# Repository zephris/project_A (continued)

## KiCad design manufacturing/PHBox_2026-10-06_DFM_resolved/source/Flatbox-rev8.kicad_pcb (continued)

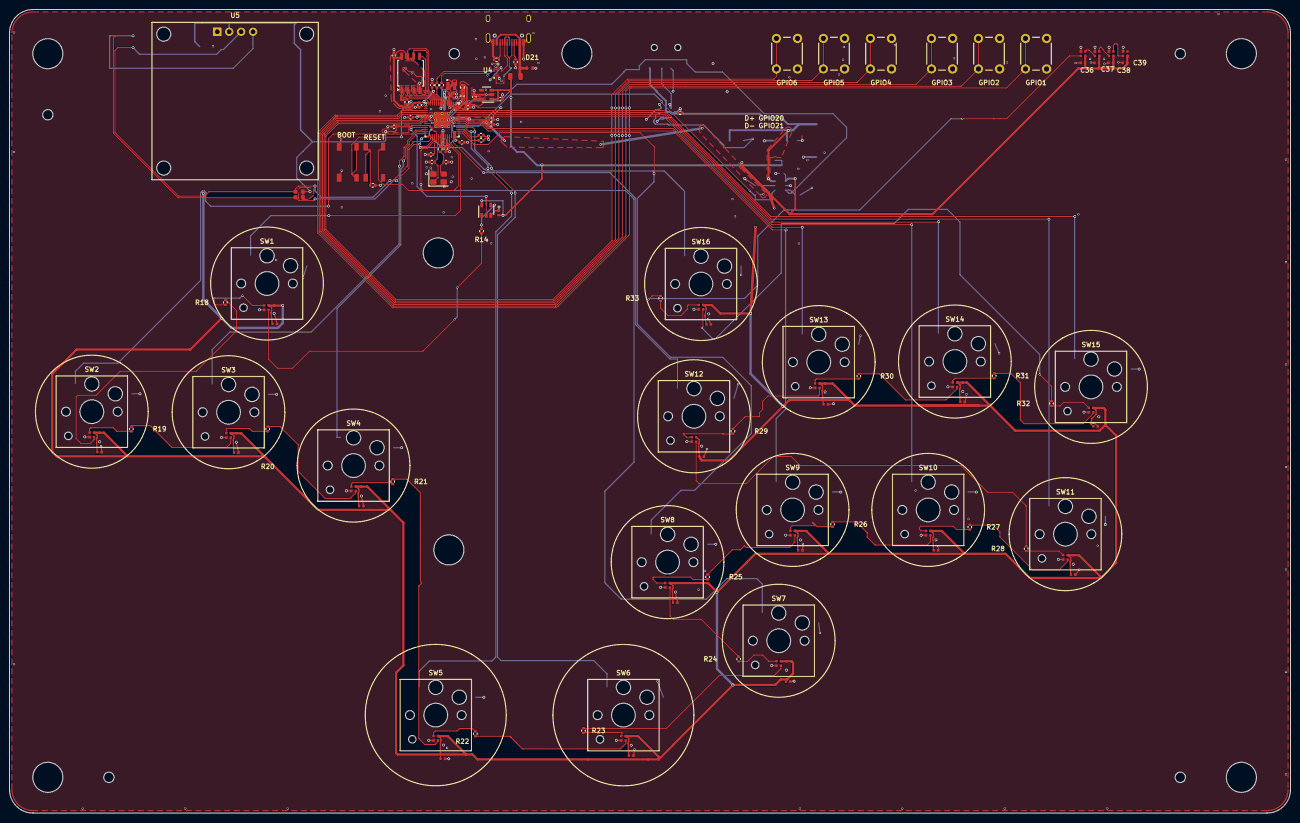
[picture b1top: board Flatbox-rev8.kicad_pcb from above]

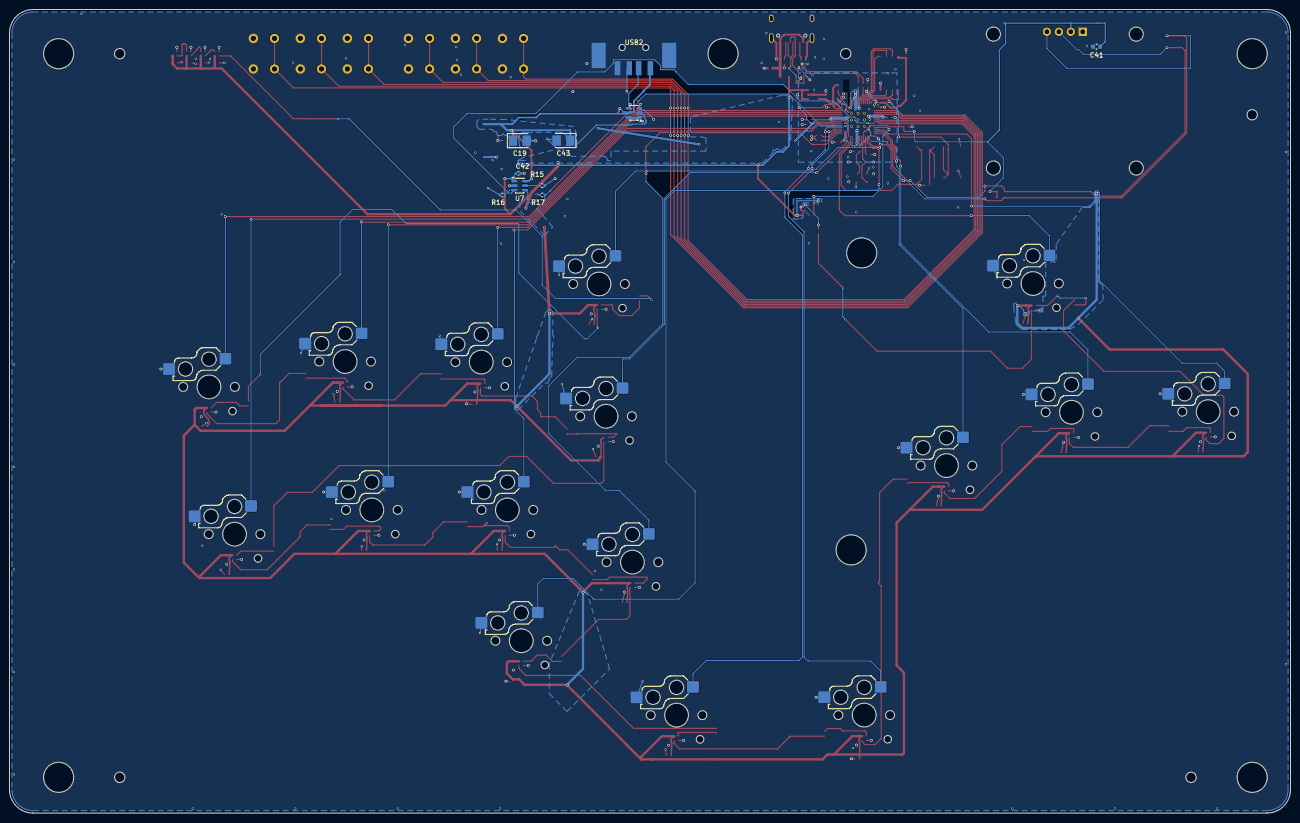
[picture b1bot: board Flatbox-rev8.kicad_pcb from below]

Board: 4 copper layers, 272.6 x 171.0 mm, 146 parts (10 on the bottom side), 97 nets.

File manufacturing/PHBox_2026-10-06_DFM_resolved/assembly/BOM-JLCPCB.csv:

Comment,Designator,Footprint,LCSC Part #,MPN,Manufacturer,Quantity
100n,"C1,C3,C4,C5,C6,C7,C8,C9,C10,C18",Capacitor_SMD:C_0402_1005Metric,C1525,,,10
4.7u,"C2,C11",Capacitor_SMD:C_0402_1005Metric,C23733,,,2
4.7u,"C12,C13",PHBox:Samsung_1005_Tolerance015,C23733,,,2
1u,"C14,C15",Capacitor_SMD:C_0402_1005Metric,C52923,,,2
15p,"C16,C17",Capacitor_SMD:C_0402_1005Metric,C1548,,,2
100u/10V,"C19,C43",PHBox:CP_KEMET_T520B_3528_21,C600583,T520B107M010ATE070,KEMET,2
100n,"C20,C21,C22,C23,C24,C25,C26,C27,C28,C29,C30,C31,C32,C33,C34,C35,C36,C37,C38,C39,C40",PHBox:Samsung_1005_Tolerance005,C1525,CL05B104KO5NNNC,Samsung Electro-Mechanics,21
100n,"C42,C44",Capacitor_SMD:C_0402_1005Metric,C1525,CL05B104KO5NNNC,Samsung Electro-Mechanics,2
SK6805-EC15,"D1,D2,D3,D4,D5,D6,D7,D8,D9,D10,D11,D12,D13,D14,D15,D16,D17,D18,D19,D20",PHBox_Repair:LED_SK6805_EC15_Optical,C2890035,SK6805-EC15,OPSCO,20
ESDA7P120-1U1M,D21,PHBox:ESDA7P120_1U1M_ST_Recommended,C2969802,ESDA7P120-1U1M,STMicroelectronics,1
750mA hold,F1,PHBox:Fuse_TECHFUSE_SMD0805_075_12V,C19108399,SMD0805-075-12V,TECHFUSE,1
3.3u,L1,lib:L_pol_2016,C42411119,,,1
33,R1,Resistor_SMD:R_0402_1005Metric,C25105,,,1
27,"R2,R3",Resistor_SMD:R_0402_1005Metric,C138021,,,2
1k,"R4,R6,R8",Resistor_SMD:R_0402_1005Metric,C11702,,,3
22,"R5,R7",Resistor_SMD:R_0402_1005Metric,C102906,,,2
5.1k,"R10,R11",Resistor_SMD:R_0402_1005Metric,C25905,,,2
4.7k,"R12,R13",PHBox:R_0603_Compact,C23162,0603WAF4701T5E,UNI-ROYAL,2
510R,R14,Resistor_SMD:R_0402_1005Metric,C25123,0402WGF5100TCE,UNI-ROYAL,1
200k 1%,R15,Resistor_SMD:R_0402_1005Metric,C25764,0402WGF2003TCE,UNI-ROYAL,1
220k,R16,Resistor_SMD:R_0402_1005Metric,C25767,0402WGF2203TCE,UNI-ROYAL,1
10k,R17,Resistor_SMD:R_0402_1005Metric,C25744,0402WGF1002TCE,UNI-ROYAL,1
100R,"R18,R19,R20,R21,R22,R23,R24,R25,R26,R27,R28,R29,R30,R31,R32,R33",Resistor_SMD:R_0402_1005Metric,C25076,0402WGF1000TCE,UNI-ROYAL,16
SW_Push,"SW19,SW20",PHBox_Repair:SW_C318884_FabOnly,C318884,,,2
RP2350_60QFN,U1,lib:RP2350-QFN-60-1EP_7x7_P0.4mm_EP3.4x3.4mm_ThermalVias,C42411118,,,1
TLV73333PDBV,U2,SOT-23-5:SOT-23-5,C134139,,,1
W25Q128JVS,U3,SOIC:SOIC-8_5.23x5.23mm_P1.27mm,C97521,,,1
ECMF2-40A100N6,U4,PHBox:ECMF2-40A100N6,C5267592,ECMF2-40A100N6,STMicroelectronics,1
HS13L03W2C01,U5,PHBox:OLED_HS13L03W2C01,C7465997,HS13L03W2C01,HS,1
SN74LV1T34DBVR,U6,SOT-23-5:SOT-23-5,C100024,SN74LV1T34DBVR,Texas Instruments,1
TPS2553DBVR,U7,Package_TO_SOT_SMD:SOT-23-6,C55266,TPS2553DBVR,Texas Instruments,1
USBLC6-2SC6,U8,Package_TO_SOT_SMD:SOT-23-6,C7519,USBLC6-2SC6,STMicroelectronics,1
HRO-TYPE-C-31-M-12,USB1,Type-C:HRO-TYPE-C-31-M-12-Assembly,C165948,,,1
USB_A,USB2,PHBox:USB_A_904-131A2032S10200,C46400,904-131A2032S10200,Jing Extension of the Electronic Co.,1
ABM8-272-T3,Y1,Crystal:Crystal_SMD_3225-4Pin_3.2x2.5mm,C20625731,,,1
1u/25V/X7R,C41,Capacitor_SMD:C_0603_1608Metric,C29936,CL10B105KA8NNNC,Samsung Electro-Mechanics,1

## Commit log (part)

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2026-02-10 Add TODO list for project enhancements
2026-02-10 Added pinout for case rgb and switch RGB, moved USB to suitable location
2026-02-11 Redone butotn layout (sort of) and localized general area for booter location
    - MAKE NEW FOOTPRINT FOR LED + SWITCH COMBO
2026-02-23 Done up switch traces for main directional and command input
    Done up switch traces for main directional and command input
    Need to redo schematic for LS RS, Up directional chaining and RGB SMD
2026-02-24 redone socket, adding RGB lighting and pathing
2026-03-09 Done up +3V3 wiring, RGB and PlayerRGB wiring
    Done up +3V3, RGB wiring and PRGB wiring, need to do fill for F.Cu and B.Cu for GND pins
2026-03-10 final design inshallah
2026-04-20 Create LICENSE
2026-04-20 Update README.md
    updated progress
